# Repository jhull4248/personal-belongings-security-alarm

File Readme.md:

# Personal-belongings-security-alarm
author: Jonathan Hull  
date: May 24, 2016  

This repository contains files for a term project on building the RC feedback oscillator shown in the following schematic.  This was the final project in ENGR12L, Engineering Circuits Lab, at Monterey Peninsula College in the Spring 2016 semester.  

The primary feature of the circuit is an RC phase shift oscillator that should produce a sine wave of about 4 kHz.  The circuit is inactive until a short circuit to ground is removed at which time a distinctive sound is emitted.  Conceptually, the wire that shorts the circuit could be attached to an item in someone's pocket and the alarm would sound if the item is removed by a thief. 

# Theoretical background

The circuit in this project generates a sine wave by looping a current through a feedback network comprised of three RC stages.  Each stage generates a 60 degree phase shift.  The result is passed to the inverting input of the opamp that provides another 180 degrees of phase shift.  The 360 degrees of phase shift plus sufficient gain from the opamp guarantees that the circuit will produce a continuous sine wave [4].  Theoretical analysis of the circuit predicts that f = sqrt(6)/(2*pi*R*C) = 3898 Hz when R=1k ohms and C=100 nF [5].

# Project steps

The project was started in late April with a target completion date of June 2, 2016.  The first step was implementation of the design in circuitlab.  This helped in understanding the circuit but unfortunately a model for the LM380 opamp could not be located and thus circuitlab could not run simulations.  Nevertheless, circuitlab does contain links that were quite useful in ordering the components needed to build a prototype.

The prototype shown below was constructed with the 14 pin version of the LM380 because it was readily available.   The prototype was initially tested with a 6V power supply because [2] indicated that it was the preferred choice.  However, that did not work correctly and a 9V supply was adopted after we observed that it was used in [1].  

An additional goal of building a printed circuit board (PCB) for the circuit was pursued at the author's own volition.  Some brief web searching showed that building a PCB requires two steps: design with a software package and sending Gerber files to a PCB manufacturer.  The manufacturer uses the Gerber files to produce the board.  After it's returned, the components are soldered onto it.

After some analysis of the available alternatives, the Eagle software PCB design package was chosen because of its popularity in the Arduino community and the fact that it's free for educational purposes.  Eagle requires the user to provide a schematic and it creates a corresponding design for a PCB.  The design shows where components are placed on the board and the precise location of tracks between each component.  The tracks correspond to wires in the prototype that will become copper traces on the PCB.

The Eagle package was relatively straightforward to use because of the excellent directions in [3].  Within a day, the following design for a 5x5cm two-layer board was complete.  The components and holes for their wires are also shown as well as the traces between holes.  The brown traces are on the top layer of the board.  The blue traces are on the bottom.

The Eagle package also outputs Gerber files.  After getting quotes from three vendors, [itead.cc](http://itead.cc) was chosen because they agreed to produce 12 "bare boards" (without components soldered on) for $9.90.  The Gerber files were uploaded to their web site on Friday May 13 and the boards were delivered on Monday May 23.  Both sides of the bare board that itead produced are shown below.

The boards were ordered from itead as a two layer PCB, 5cm x 5cm max, 1.6mm thick, HASL surface finish, 100% E-test, and 1 oz. thick copper.  The traces were 10mil wide with 20mil minimum space between traces.  These are normal parameters and were perfectly adequate for this design.

The final version of the board shown below was produced by soldering the components on one of the bare boards.  Happily, this worked correctly the first time.  Needless to say, this was a huge relief since a mistake could only be corrected with another ten day turnaround from itead.

# Experimental Results

Verification of the theoretical prediction that the circuit would produce a 4 kHz sine wave was done by connecting the first channel of the Digilent Analog Discovery 2 USB oscilloscope to the speaker terminals.  The voltage trace is shown below.  We see a waveform that's shaped like a sine wave, but not as smooth as it should be.  The frequency of the waveform is 4.09 kHz which is within about 4.8% ((|3898-4087|/3898)*100) of the theoretically predicted value of 3.90 kHz.  A video illustrating the operation of the circuit is available at https://youtu.be/Xsj34tHOlkY

# Files

The Eagle schematic, board file and Gerber files in the format required by itead are in this github repository.

# Conclusions

This project shows how a sine wave can be generated with a handful of low cost components and is an excellent example of a circuit with practical applications.  Production of the PCB was an interesting addition to the project that shows how an abstract design expressed in a schematic can be reduced to a form that could be used in a real product.  First hand knowledge of this process is something that every electrical enginer and computer scientist should have as they progress through their career and imagine different ways in which their ideas could end up in a product that normal people would pay for.  A printed circuit board is one way that could happen.  

# References

[1].  N. Alsbou, K. Al-Olimat, V. Labay, and H. LeBlanc, "Introducing Students to Electronic Devices and Electric Circuit Applications at Early Level in the Engineering Curriculum through Multiple Projects,"  122nd ASEE Annual Conference and Exposition, Seattle, WA, June 14-17, 2015. https://www.asee.org/public/conferences/56/papers/12964/download.

[2]. "Pull Pin Security Alarm System," http://www.electronicshub.org/pull-pin-security-alarm-system/, Aug. 5, 2015.

[3].  S. Monk, Make your own PCBs with Eagle: from schematic designs to finished boards, McGraw-Hill, 2014.

[4]. Electronic Oscillators and its Feedback Network, https://www.youtube.com/watch?v=aAiZsJz4UW8&feature=youtu.be

[5]. Gate 2003 ECE Op Amp RC phase shift oscillator, https://www.youtube.com/watch?v=BdULnwS91ts&feature=youtu.be

# Additional background references

[a].  RC Phase Shift Oscillator, http://www.visionics.a.se/html/curriculum/Experiments/RC%20Phase%20Shift%20Oscillator/RC%20Phase%20Shift%20Oscillator1.html

[b].  How do Sinusoidal Oscillations Arise in RC Oscillators, https://www.researchgate.net/post/How_do_sinusoidal_oscillations_arise_in_RC_oscillators#share

[c]. What is the Basic Idea of a Wien Bridge Oscillator?, https://www.researchgate.net/post/What_is_the_basic_idea_of_Wien_bridge_oscillator_How_does_it_operate

[d]. Sine Wave Oscillator using LM741 (contains concise description of Barkhausen Criteria), http://www.engineersgarage.com/contribution/sine-wave-oscillator-using-lm741

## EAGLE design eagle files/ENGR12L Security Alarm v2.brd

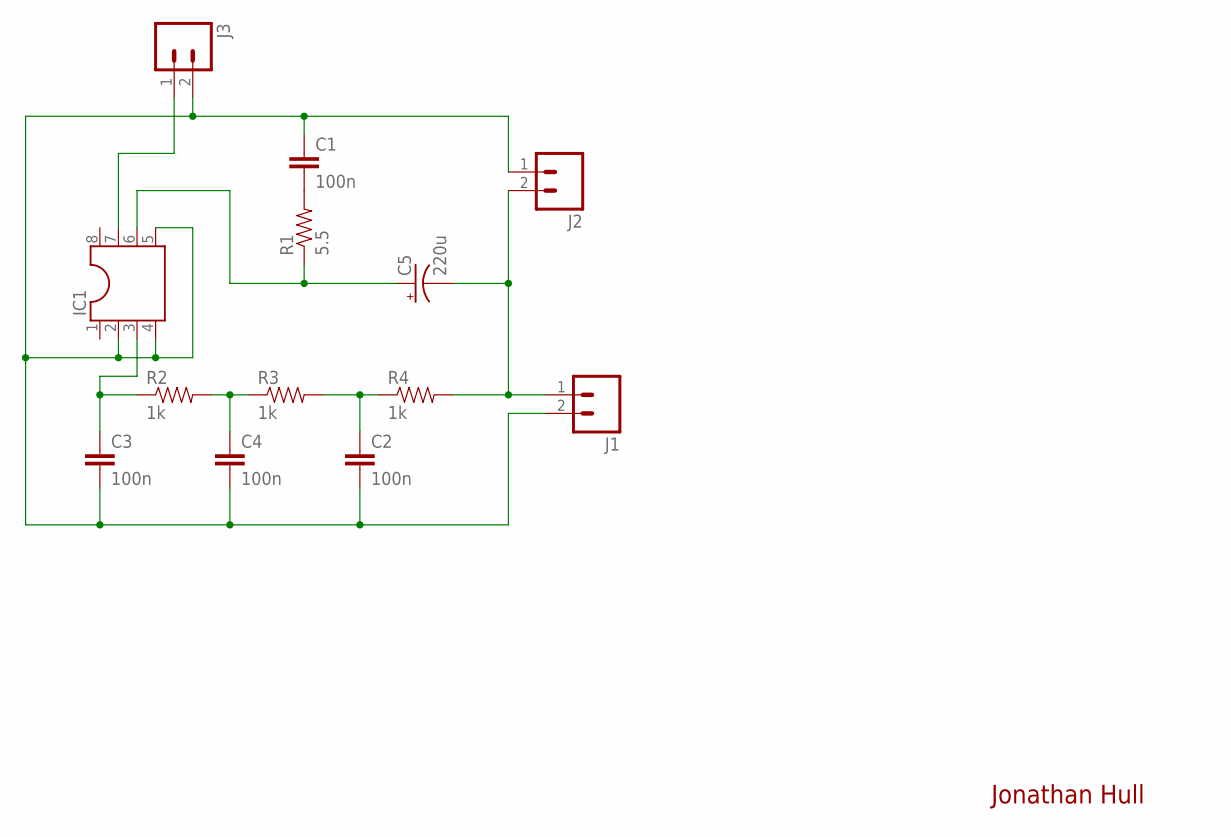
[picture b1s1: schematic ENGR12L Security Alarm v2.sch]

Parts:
C1, C2, C3, C4: 100n; CAP-PTH-SMALL
C5: 220u; CPOL-RADIAL-10UF-25V
IC1: DIL8S; SOCKET-08
J1, J2, J3: M023.5MM; SCREWTERMINAL-3.5MM-2
R1: 5.5; AXIAL-0.4
R2, R3, R4: 1k; AXIAL-0.4

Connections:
GND: C1.1, C2.2, C3.2, C4.2, IC1.2, IC1.4, IC1.5, J1.2, J2.1, J3.2
unnamed: C1.2, R1.P$2 (2)
unnamed: IC1.7, J3.1
unnamed: C4.1, R2.P$2 (2), R3.P$1 (1)
unnamed: C2.1, R3.P$2 (2), R4.P$1 (1)
unnamed: C3.1, IC1.3, R2.P$1 (1)
unnamed: C5.2 (-), J1.1, J2.2, R4.P$2 (2)
unnamed: C5.1 (+), IC1.6, R1.P$1 (1)

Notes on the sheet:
Jonathan Hull

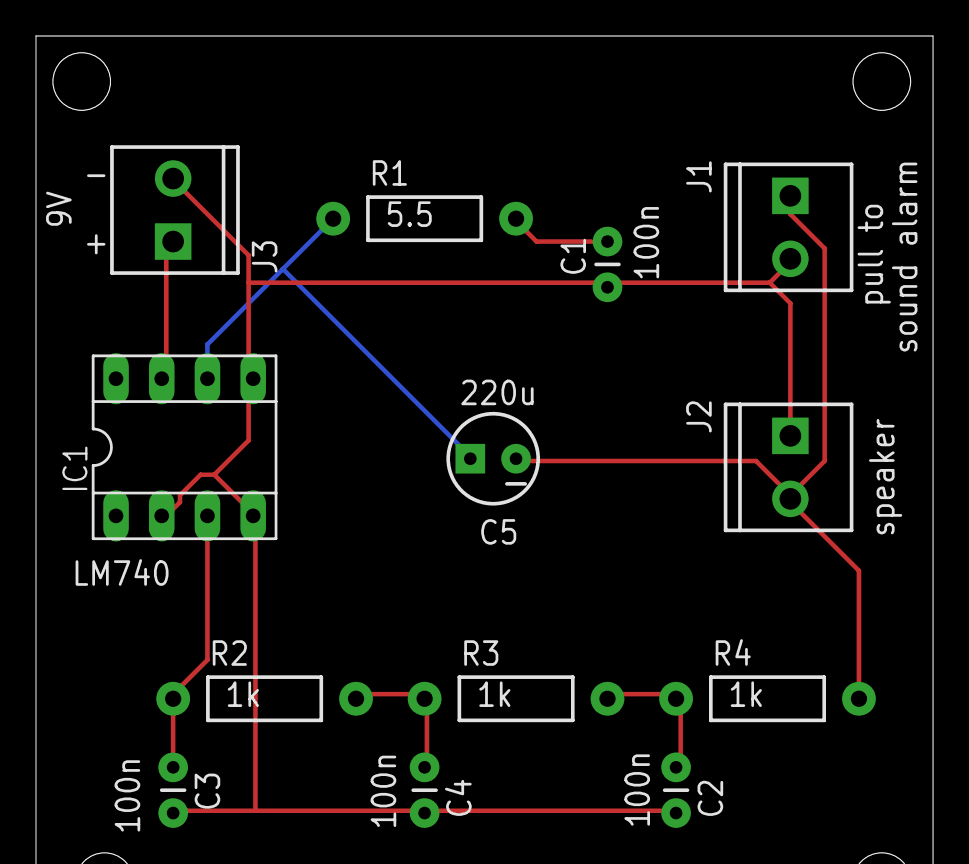
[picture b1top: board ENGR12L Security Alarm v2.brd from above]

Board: 2 copper layers, 13 parts (0 on the bottom side), 8 nets.

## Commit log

2016-05-24 :lollipop: Added .gitattributes & .gitignore files
2016-05-25 second commit
2016-05-25 third commit
2016-05-25 fourth commit
2016-06-15 fix typo

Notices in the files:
parts and their libraries:
SparkFun-Capacitors: Licensing: Creative Commons ShareAlike 4.0 International - https://creativecommons.org/licenses/by-sa/4.0
